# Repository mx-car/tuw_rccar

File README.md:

## RaceCar Tutorial
### Setup the RaceCar:
This tutorial is designed for xubuntu (16.04) in usage with ROS Kinetic.
#### .bashrc:

```
export ARDUINO_ROOT=$HOME/opt/arduino     # to arduino 1.7.8
export VEHICLE_TYPE=1                     # 1 for race car 2 for crawler
export RCCAR_DIR=$HOME/projects/rccar     # your project root with ros workspaces
source $RCCAR_DIR/ws02/devel/setup.bash   # to source your workspace
```
#### ROS Installation:
A full manual on how to install ROS Kinetic on the device can be found at the [ROS Tutorial](http://wiki.ros.org/kinetic/Installation/Ubuntu).
#### ROS Nodes:
- Addidinal pkgs needed
```
sudo apt-get install ros-kinetic-joy
```
- Additionally you need to install the following Packages from the tuw-robotics GitHub page:
```
mkdir -p $RCCAR_DIR/ws01/src
cd $RCCAR_DIR/ws01/src
git clone https://github.com/tuw-robotics/tuw_geometry.git
git clone https://github.com/tuw-robotics/tuw_teleop.git
git clone https://github.com/tuw-robotics/tuw_msgs.git
cd $RCCAR_DIR/ws01
catkin_make
source $RCCAR_DIR/ws01/devel/setup.bash
mkdir -p $RCCAR_DIR/ws02/src
cd $RCCAR_DIR/ws02/src
git clone https://github.com/tuw-robotics/tuw_arduino_ros.git
cd $RCCAR_DIR/ws02
catkin_make
```

#### Arduino Setup: 
- Set root rights to the USB by preparing or creating the file: `/etc/udev/rules.d/98-openocd.rules` with the following content:

```
ACTION!="add|change", GOTO="openocd_rules_end"
SUBSYSTEM!="usb|tty|hidraw", GOTO="openocd_rules_end"

#Please keep this list sorted by VID:PID

#CMSIS-DAP compatible adapters
ATTRS{product}=="*CMSIS-DAP*", MODE="664", GROUP="plugdev"

LABEL="openocd_rules_end"
```
    
- Get the Arduino IDE Version 1.7.8 (newer ones are actuelly not supported).
untar the IDE to `$HOME/opt/` and make a soft link `$HOME/opt/arduino` 
Download Link: https://roblab.auto.tuwien.ac.at/owncloud/index.php/s/ZcFlfoNaCEYlrYR
```
mkdir -p $HOME/opt/
tar -xzvf arduino-1.7.8-linux64.tar.xz.part $HOME/opt/
cd $HOME/opt/
ln -s arduino-1.7.8-linux64 $ARDUINO_ROOT  # ARDUINO_ROOT must be exported in .bashrc
```
- check your vehicle type using `echo $VEHICLE_TYPE` 1 = RaceCar and 2 RocketCrawler.
```
mkdir -p $RCCAR_DIR/ws02/src/tuw_arduino_ros/tuw_arduino_bridge/arduino/build
cd $RCCAR_DIR/ws02/src/tuw_arduino_ros/tuw_arduino_bridge/arduino/build
cmake ..
make firmware_motion_demo.upload
```
 - Note:
      The tuw_arduino_bridge package holds deprecated ROS nodes which were used a while ago with shmFw. These nodes are no longer required. The important part of the tuw_arduino_bridge package is the firmware folder.

### Set the RaceCar into operation:
**Note:** this guide refers to the RaceCars deployed at TU-Wien Treidlstrasse 3, 4th Floor.
#### Connect:
  Connect your Computer to the "humans" wifi, you can Login with your TU e-mail address and your TU password (like the "tuwel" wifi).
    Troubleshooting:
      The "humans" network does not work very reliable.
      If you can not connect to "humans" you can try to connect to the "robots" wifi, ask for the Password.
#### Setup the RaceCar: 
  Connect the IntelUp with the Arduino Board (USB 2.0 to Micro USB "programming").
    Troubleshooting:
      Check the connection wire, it needs to be a data (not a power only) wire.
      Check if the "programming" port of the Arduino is connected. You do not want to use the "native" port.

  Connect the motor controller board with the power switch (the power switch is located under the Arduino).
  Connect the battery with the power switch (the power switch is located under the Arduino).
  Connect the IntelUp with the Logitech F510 gamepad (the wired one).
  Provide the IntelUp with power. You can either use the power supply for the IntelUp or power it with the Amazon Basics battery pack, use the 3.4A output (the output with the double bolt).
  Connect the serve motor (which is responsible for the steering) with the motor controller board.
    Optional:
      Connect the IntelUp with the RealSense R200 camera. Use the USB 3.0 Micro-B to USB 3.0 Micro-B cable only! Other cables like combinations of adapters from USB 3.0 Micro-B to USB 3.0 A with an other USB 3.0 A to USB 3.0 Micro-B are very likely to fail.
      Connect the IMU with the motor controller board (ground is not connected).
#### Run the RaceCar:
  SSH connect to "robot" at the RaceCar (IP-address: 192.168.10.53), ask for the password of the IntelUp.
    Troubleshooting:
      Check if your computer is connected to "humans" wifi or "robots" wifi.
      Check if the RaceCar is connected to the "robots" wifi.
      Check if the RaceCar got the IP-address provided above.
  Switch on the power for the motor controller board.
  Run the following command on the RaceCar:
    ```
    roslaunch tuw_rccar arduino_ros_demo.launch
    ```
    
#### Setup IntelUp:
  Install xubuntu (16.04) or any other related distribution (also 16.04).
  Optional:
    This step is not necessary for the Realsense R200 to work but might help in Troubleshooting.
    Follow the steps 5 and 6 (replace step to with the OS of your choice): [IntelUp Tutorial](https://01.org/developerjourney/recipe/intel-realsense-robotic-development-kit) (last accessed: 08.05.2017)
    
#### Run the Realsense:

```
sudo apt-get install ros-kinetic-realsense-camera
sudo apt-get install ros-kinetic-joy
```

```
roslaunch realsense_camera r200_nodelet_default.launch
```

  Now you should be able to control the RaceCar with the gamepad, usually one of the buttons RB, LB, RT, LT is a deadman's button.
  Running the following command on your device allows you to access the ROS core of the IntelUp (change IP-adress to the IP-adress (in the "robots" wifi) of the IntelUp):
    ```
    export ROS_MASTER_URI=http://192.168.10.53:11311
    ```

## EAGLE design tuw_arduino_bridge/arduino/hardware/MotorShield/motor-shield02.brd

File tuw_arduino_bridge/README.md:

## PREINSTALL:
### Arduino Firmware
``` 
export ARDUINO_ROOT=/opt/arduino-1.7.8-linux64
or 
export ARDUINO_ROOT=$HOME/opt/arduino
or 
export ARDUINO_ROOT=/somewhere/else
``` 
### PC Programms
Install shmFw
``` 
export SHMFW=$HOME/shmfw/
export SHMFW=/somewhere/else
``` 

### Different Vehicles
To distinguish between the different vehicles, you have to set an environment variable
according to your current configuration:
```
Racecar:   export VEHICLE_TYPE=1
RocketCrawler:    export VEHICLE_TYPE=2
```
(Be sure to run ```cmake ..``` after changing the vehicle type)

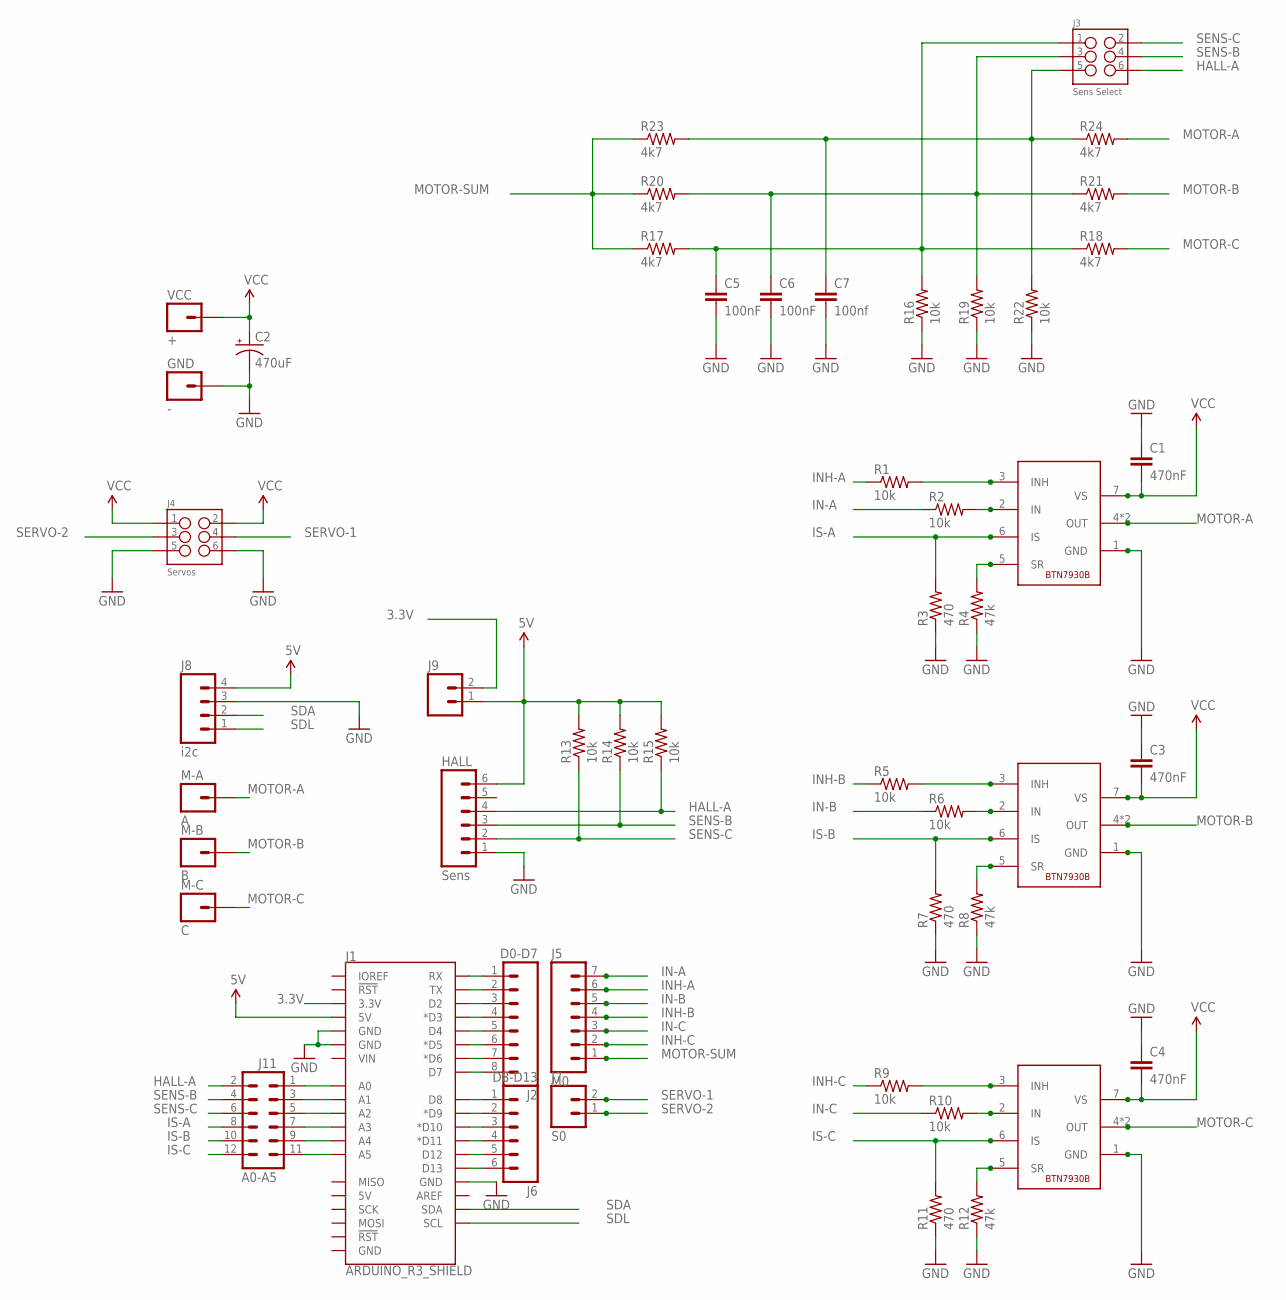
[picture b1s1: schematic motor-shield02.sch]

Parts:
C1, C3, C4: 470nF; CAP-PTH-SMALLEZ
C2: 470uF; CPOL-RADIAL-100UF-25V
C5, C6: 100nF; CAP-PTH-SMALLEZ
C7: 100nf; CAP-PTH-SMALLEZ
DA: H-Bridge; INF-PG-TO263-7-1_L_1PRIMARY
DB: H-Bridge; INF-PG-TO263-7-1_L_1PRIMARY
DC: H-Bridge; INF-PG-TO263-7-1_L_1PRIMARY
GND: -; SMTRA-256-8-6
HALL: Sens; 1X06-1MM
J1: ARDUINO_R3_SHIELD; UNO_R3_SHIELD_ICSP
J2: D0-D7; 1X08_NO_SILK
J3: Sens Select; 2X3
J4: Servos; 2X3
J5: M0; 1X07_NO_SILK
J6: D8-D13; 1X06_NO_SILK_YES_STOP
J7: S0; 1X02_NO_SILK
J8: i2c; 1X04_NO_SILK_ALL_ROUND
J9: M021X02_NO_SILK; 1X02_NO_SILK
J11: A0-A5; 2X6
M-A: A; SMTRA-256-8-6
M-B: B; SMTRA-256-8-6
M-C: C; SMTRA-256-8-6
R1, R2, R5, R6, R9, R10, R13, R14, R15, R16, R19, R22: 10k; AXIAL-0.3
R3, R7, R11: 470; AXIAL-0.3
R4, R8, R12: 47k; AXIAL-0.3
R17, R18, R20, R21, R23, R24: 4k7; AXIAL-0.3
VCC: +; SMTRA-256-8-6

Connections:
3.3V: J1.3.3V, J9.2
5V: HALL.6, J1.5V, J8.4, J9.1, R13.P$2 (2), R14.P$2 (2), R15.P$2 (2)
GND: C1.1, C2.2 (-), C3.1, C4.1, C5.2, C6.2, C7.2, DA.1 (GND), DB.1 (GND), DC.1 (GND), GND.P$1, HALL.1, J1.GND@0 (GND), J1.GND@1 (GND), J1.GND@2 (GND), J4.5, J4.6, J8.3, R3.P$1 (1), R4.P$1 (1), R7.P$1 (1), R8.P$1 (1), R11.P$1 (1), R12.P$1 (1), R16.P$1 (1), R19.P$1 (1), R22.P$1 (1)
HALL-A: HALL.4, J3.6, J11.2, R15.P$1 (1)
IN-A: J5.7, R2.P$1 (1)
IN-B: J5.5, R6.P$1 (1)
IN-C: J5.3, R10.P$1 (1)
INH-A: J5.6, R1.P$1 (1)
INH-B: J5.4, R5.P$1 (1)
INH-C: J5.2, R9.P$1 (1)
IS-A: DA.6 (IS), J11.8, R3.P$2 (2)
IS-B: DB.6 (IS), J11.10, R7.P$2 (2)
IS-C: DC.6 (IS), J11.12, R11.P$2 (2)
MOTOR-A: DA.4 (OUT), DA.8 (OUT), M-A.P$1, R24.P$2 (2)
MOTOR-B: DB.4 (OUT), DB.8 (OUT), M-B.P$1, R21.P$2 (2)
MOTOR-C: DC.4 (OUT), DC.8 (OUT), M-C.P$1, R18.P$2 (2)
MOTOR-SUM: J5.1, R17.P$1 (1), R20.P$1 (1), R23.P$1 (1)
unnamed: DA.3 (INH), R1.P$2 (2)
unnamed: DA.2 (IN), R2.P$2 (2)
unnamed: DB.3 (INH), R5.P$2 (2)
unnamed: DA.5 (SR), R4.P$2 (2)
unnamed: DB.2 (IN), R6.P$2 (2)
unnamed: DB.5 (SR), R8.P$2 (2)
unnamed: DC.3 (INH), R9.P$2 (2)
unnamed: DC.2 (IN), R10.P$2 (2)
unnamed: DC.5 (SR), R12.P$2 (2)
unnamed: J1.A0, J11.1
unnamed: J1.A1, J11.3
unnamed: J1.A2, J11.5
unnamed: J1.RX, J2.1
unnamed: J1.TX, J2.2
unnamed: J1.D2, J2.3
unnamed: J1.D3 (*D3), J2.4
unnamed: J1.D4, J2.5
unnamed: J1.D5 (*D5), J2.6
unnamed: J1.D6 (*D6), J2.7
unnamed: J1.D7, J2.8
unnamed: J1.D8, J6.1
unnamed: J1.D9 (*D9), J6.2
unnamed: J1.D10 (*D10), J6.3
unnamed: J1.D11 (*D11), J6.4
unnamed: J1.D12, J6.5
unnamed: J1.D13, J6.6
unnamed: J1.A3, J11.7
unnamed: J1.A4, J11.9
unnamed: J1.A5, J11.11
unnamed: C5.1, J3.1, R16.P$2 (2), R17.P$2 (2), R18.P$1 (1)
unnamed: C6.1, J3.3, R19.P$2 (2), R20.P$2 (2), R21.P$1 (1)
unnamed: C7.1, J3.5, R22.P$2 (2), R23.P$2 (2), R24.P$1 (1)
SDA: J1.SDA, J8.2
SDL: J1.SCL, J8.1
SENS-B: HALL.3, J3.4, J11.4, R14.P$1 (1)
SENS-C: HALL.2, J3.2, J11.6, R13.P$1 (1)
SERVO-1: J4.4, J7.2
SERVO-2: J4.3, J7.1
VCC: C1.2, C2.1 (+), C3.2, C4.2, DA.7 (VS), DB.7 (VS), DC.7 (VS), J4.1, J4.2, VCC.P$1

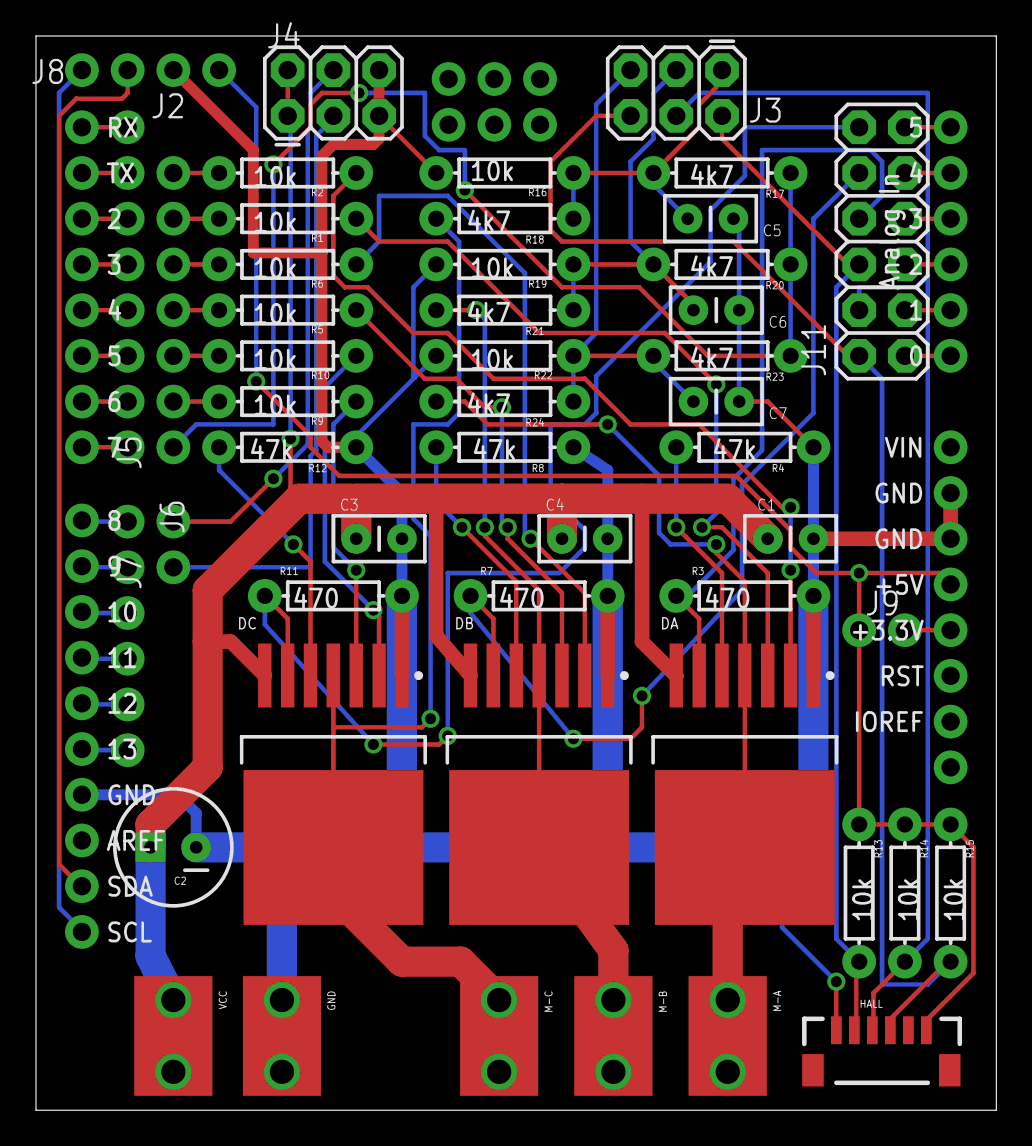
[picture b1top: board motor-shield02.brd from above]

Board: 2 copper layers, 53.4 x 59.7 mm, 50 parts (0 on the bottom side), 56 nets.

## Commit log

2016-11-16 Metapackage information to CMakeList added
2016-11-17 q&d merged existing code, teleop is possible NO firmware included
2016-11-24 Use IWS-msgs for control.
2016-11-29 Cosmetic: unify syntax, code cleanup
2016-11-29 Delay between restart attempts of serial link.
2016-12-01 Added service for reading ackermann configuration Added first publisher of IMU data
2016-12-01 Fix segfault on node termination.
2017-02-06 Just for testing
2017-06-26 added tuw_arduino_ros as subfolder
2017-06-26 Readme.md for RaceCar added
2018-04-09 JointCmd Topic renamed and format checks added
2018-04-09 docu update
2018-07-12 hardware design added
2018-07-12 hardware readme added
2018-09-12 Changed type of rccar read messages from Twist to TwistStamped.

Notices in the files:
parts and their libraries:
SparkFun-Capacitors: Licensing: Creative Commons ShareAlike 4.0 International - https://creativecommons.org/licenses/by-sa/4.0
